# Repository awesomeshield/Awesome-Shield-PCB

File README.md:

# Awesome Shield PCB

This repo is for Awesome Shield hardware development.

## Branches

The branch `unusedVariants` is used to retain version history of variants that have been deprecated.

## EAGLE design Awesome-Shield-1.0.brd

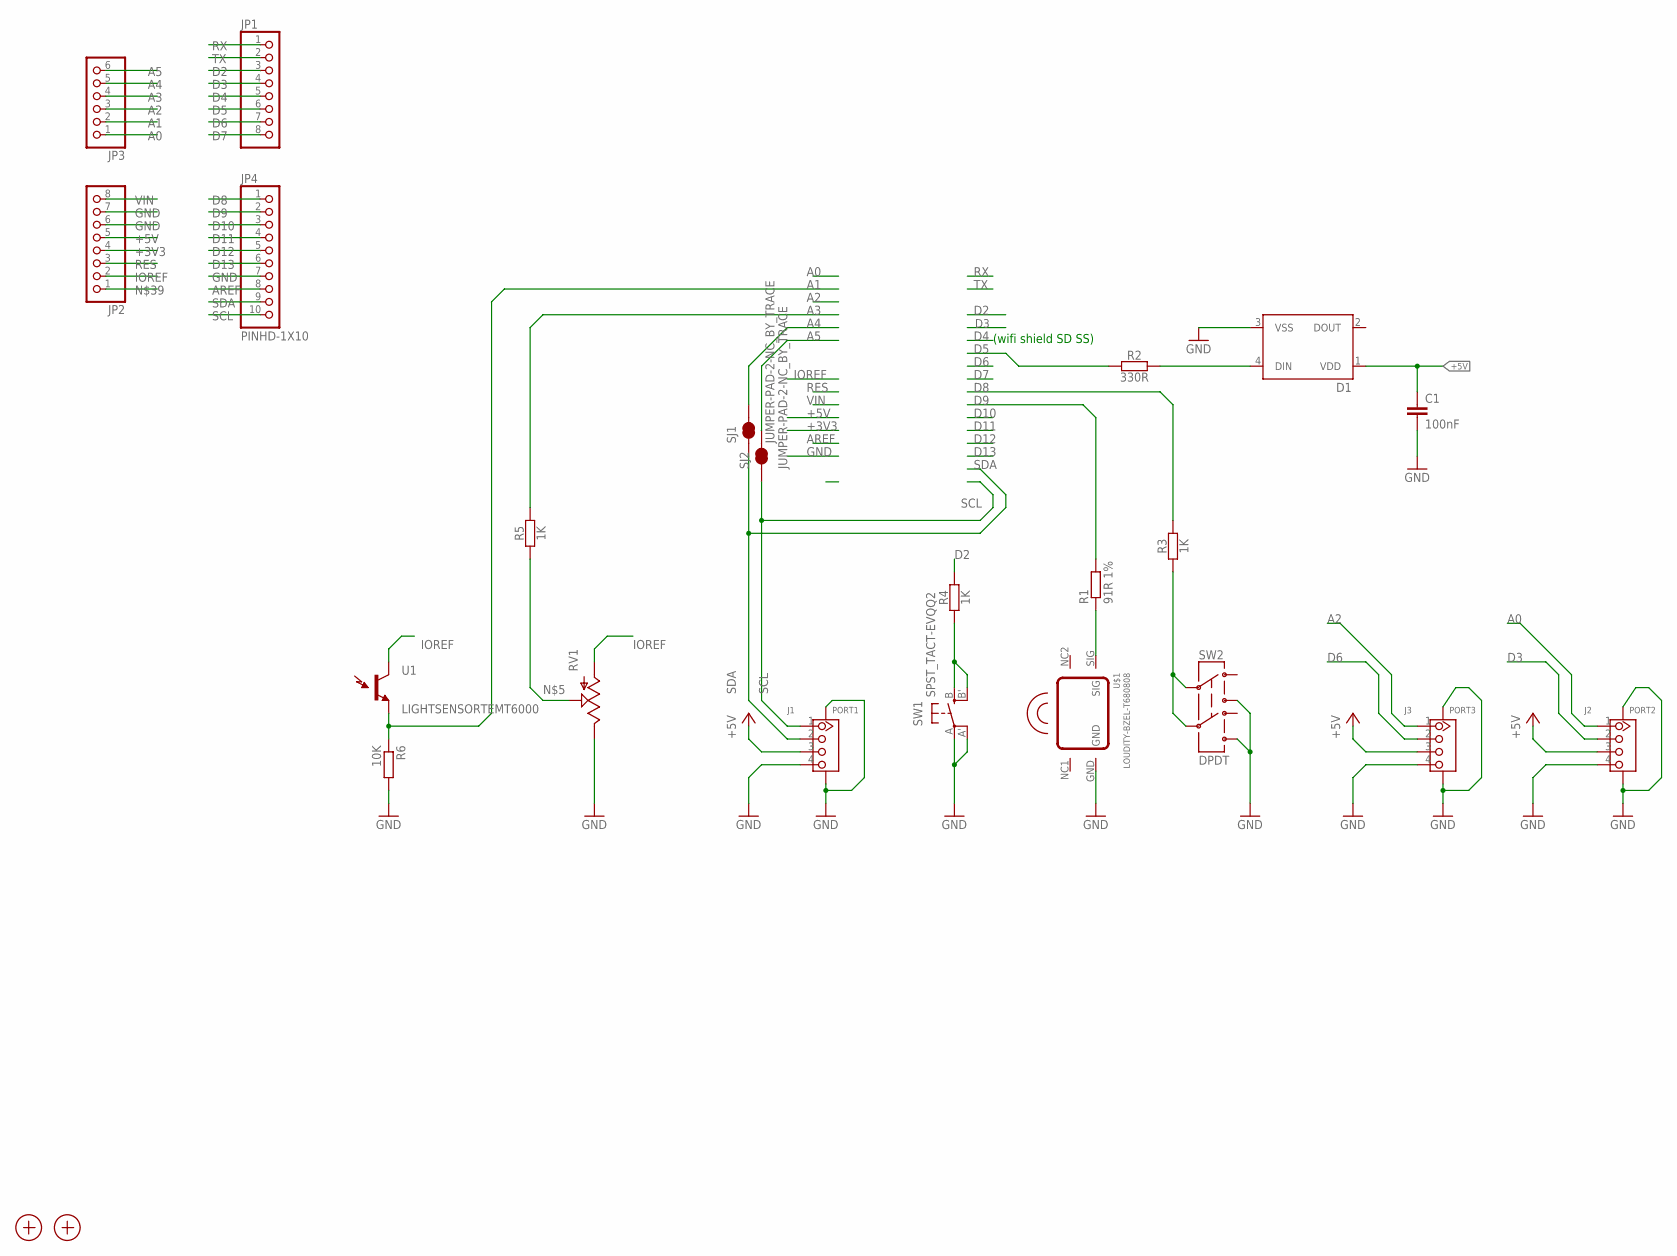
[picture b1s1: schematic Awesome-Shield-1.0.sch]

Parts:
C1: 100nF; C0603
D1: WS2812B
J1: PORT1; HW4-SMD-2.0
J2: PORT2; HW4-SMD-2.0
J3: PORT3; HW4-SMD-2.0
JP1, JP2: PINHD-1X8CLEANBIG; 1X08-CLEANBIG
JP3: PINHD-1X6CLEAN; 1X06-CLEAN
JP4: PINHD-1X10; 1X10-BIG
R1: 91R 1%; R1206
R2: 330R; C1206
R3, R4, R5: 1K; C0603
R6: 10K; R1206
RV1: POT; ALPS_POT
SJ1, SJ2: JUMPER-PAD-2-NC_BY_TRACE; PAD-JUMPER-2-NC_BY_TRACE_YES_SILK
SW1: SPST_TACT-EVQQ2; EVQ-Q2
SW2: DPDT; AYZ0202
U1: LIGHTSENSORTEMT6000; TEMT6000-SEN
U$1: LOUDITY-BZEL-T680808; SMT-68
X1, X2: PASSER-07; PASSER_07MM

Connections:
+3V3: JP2.4
+5V: C1.1, D1.1 (VDD), J1.3, J2.3, J3.3, JP2.5
A0: J2.1, JP3.1
A1: JP3.2, R6.1, U1.EMITTER (E1)
A2: J3.1, JP3.3
A3: JP3.4, R5.2
A4: JP3.5, SJ1.2
A5: JP3.6, SJ2.2
AREF: JP4.8
D2: JP1.3, R4.2
D3: J2.2, JP1.4
D4: JP1.5
D5: JP1.6, R2.1
D6: J3.2, JP1.7
D7: JP1.8
D8: JP4.1, R3.2
D9: JP4.2, R1.2
D10: JP4.3
D11: JP4.4
D12: JP4.5
D13: JP4.6
GND: C1.2, D1.3 (VSS), J1.4, J1.SS1, J1.SS2, J2.4, J2.SS1, J2.SS2, J3.4, J3.SS1, J3.SS2, JP2.6, JP2.7, JP4.7, R6.2, RV1.P$1 (E), SW1.A, SW1.A' (P1), SW2.3, SW2.6, U$1.GND
IOREF: JP2.2, RV1.P$3 (A), U1.COLLECTOR (C1)
unnamed: R1.1, U$1.SIG
unnamed: D1.4 (DIN), R2.2
unnamed: R3.1, SW2.2, SW2.5
unnamed: R5.1, RV1.P$2 (S)
unnamed: R4.1, SW1.B (S), SW1.B' (S1)
RES: JP2.3
RX: JP1.1
SCL: J1.1, JP4.10, SJ2.1
SDA: J1.2, JP4.9, SJ1.1
TX: JP1.2
VIN: JP2.8

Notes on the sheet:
(wifi shield SD SS)

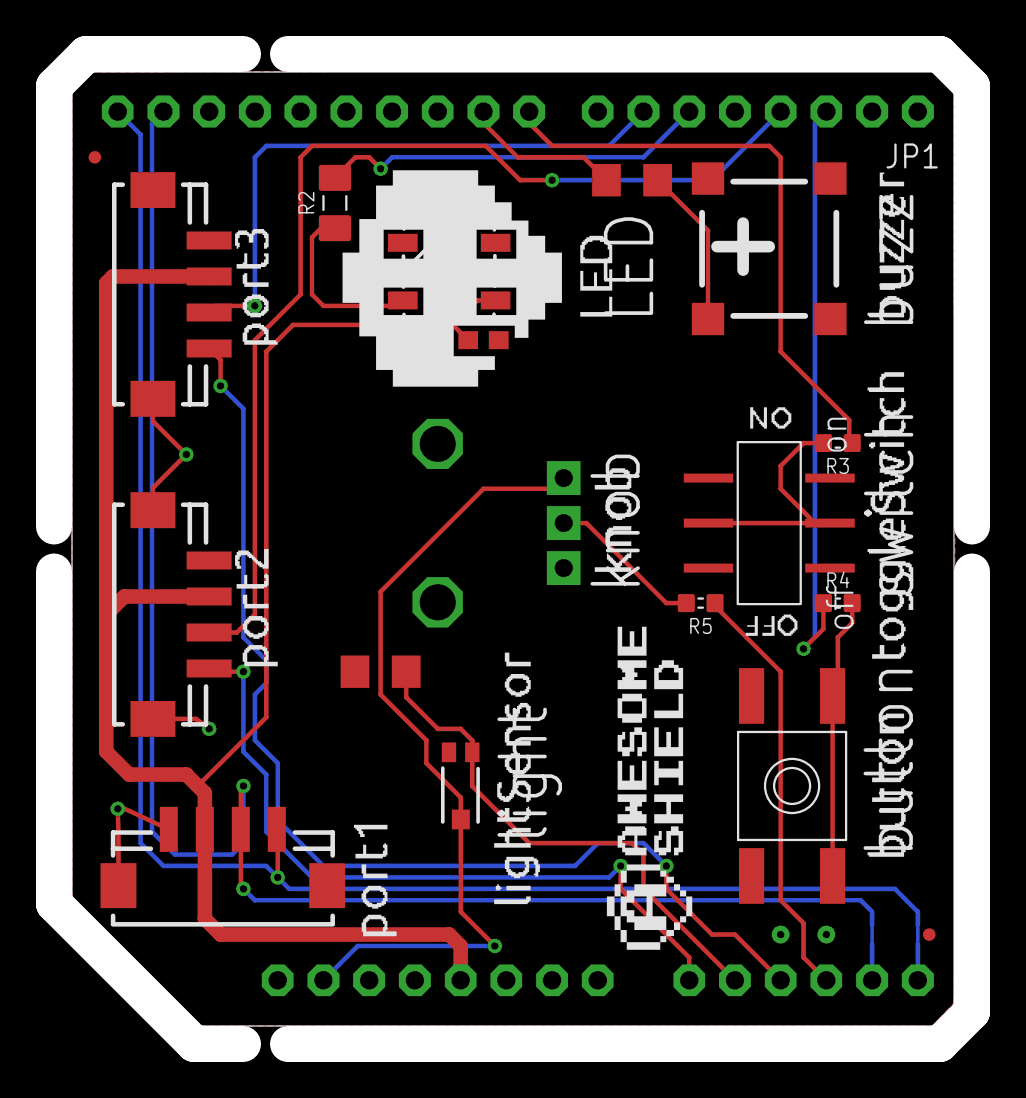
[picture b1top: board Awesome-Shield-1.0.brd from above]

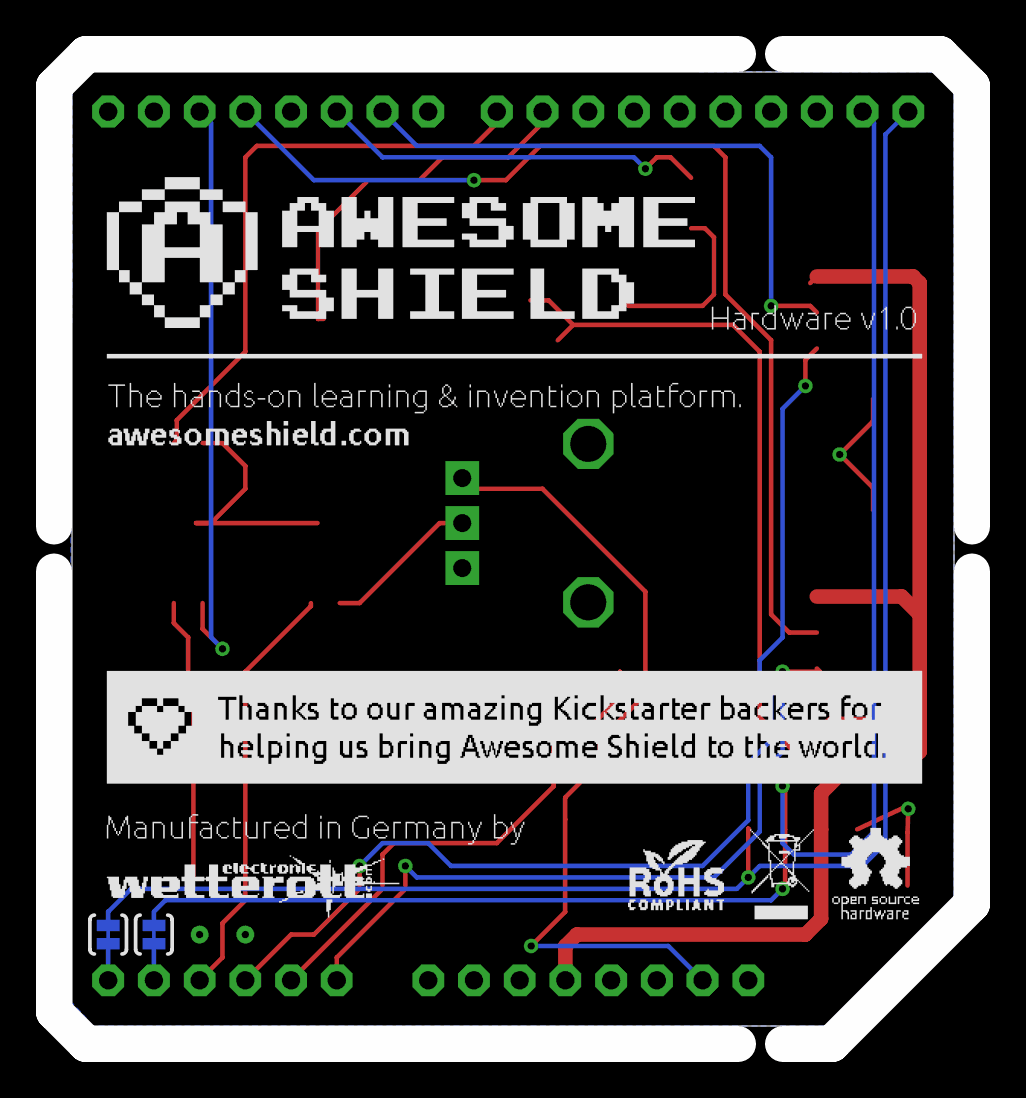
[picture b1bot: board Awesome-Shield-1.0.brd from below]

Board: 2 copper layers, 51.0 x 55.0 mm, 24 parts (2 on the bottom side), 22 nets.

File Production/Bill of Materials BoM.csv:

Manufacturer,Manufacturer Part Number (MPN),REFDES,Quantity,Mount Type,Package,Specs,Data Sheet,Notes
"Shenzhen NS-Tech Co.,Ltd.",1125S-SMT-4P,"J1, J2, J3",3,SMT,4pin connector,"4pin connector, pitch 2.00mm",http://www.seeedstudio.com/depot/images/opl/datasheet/347009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,Manufacturer page: http://www.nstech.com.cn/en/products_1.asp?menuid=19&menuid2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
4UConnector,18164,"JP1, JP2",2,THT,socket header,"1x8, 2.54mm pitch",http://www.4uconnector.com/online/object/4udrawing/18164.pdf,
4UConnector,18169,JP3,1,THT,socket header,"1x6, 2.54mm pitch",http://www.4uconnector.com/online/object/4udrawing/18169.pdf,
4UConnector,18163,JP4,1,THT,socket header,"1x10, 2.54mm pitch",http://www.4uconnector.com/online/object/4udrawing/18163.pdf,
Shenzhen Worldsemi Co.,ws2812b,LED1,1,SMT,5050,RGB,http://www.seeedstudio.com/document/pdf/WS2812B%20Datasheet.pdf,
Panasonic Electronic Components,ERJ-8GEYJ103V,R6,1,SMT,1206,10K,http://industrial.panasonic.com/ww/products/resistors/chip-r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,
AVX,0603YC104KAT2A,C1,1,SMT,0603,100nF,http://www.tme.eu/en/Document/667fe6e7748c0ed1675574c6bf64b7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,
Royal Ohm,1206S4F910JT5E,R1,1,SMT,1206,91R +/- 1%,http://www.tme.eu/en/Document/13f9d0766a2524c5bd28b9996aed3c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,
ALPS,RK09K1130A8G,RV1,1,THT,"vertical mount, pot",10K,http://www.alps.com/prod/info/E/HTML/Potentiometer/RotaryPot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,
LOUDITY,LD-BZEL-T68-0808,SG1,1,SMT,8.5 x 8.5 x 3.6mm,,http://www.tme.eu/de/Document/4d922506d0f83f2ef88b8a517d03f5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,buzzer
Schurter,1301.9314,SW1,1,SMT,"square, gull wing",TACT,http://www.schurter.com/bundles/snceschurter/epim/_ProdPool_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,
TME,MSS-2235S,SW2,1,SMT,"rect, gull wing","slide, DPDT",http://www.tme.eu/en/details/mss-2235s/slide-switches/,
Vishay,TEMT6000X01,U1,1,SMT,1206,,http://www.vishay.com/docs/81579/temt6000.pdf,
,,R2,1,SMT,1206,330R,,
,,"R3, R4, R5",3,SMT,1603,1K,,
TOTAL,,,16,,,,,

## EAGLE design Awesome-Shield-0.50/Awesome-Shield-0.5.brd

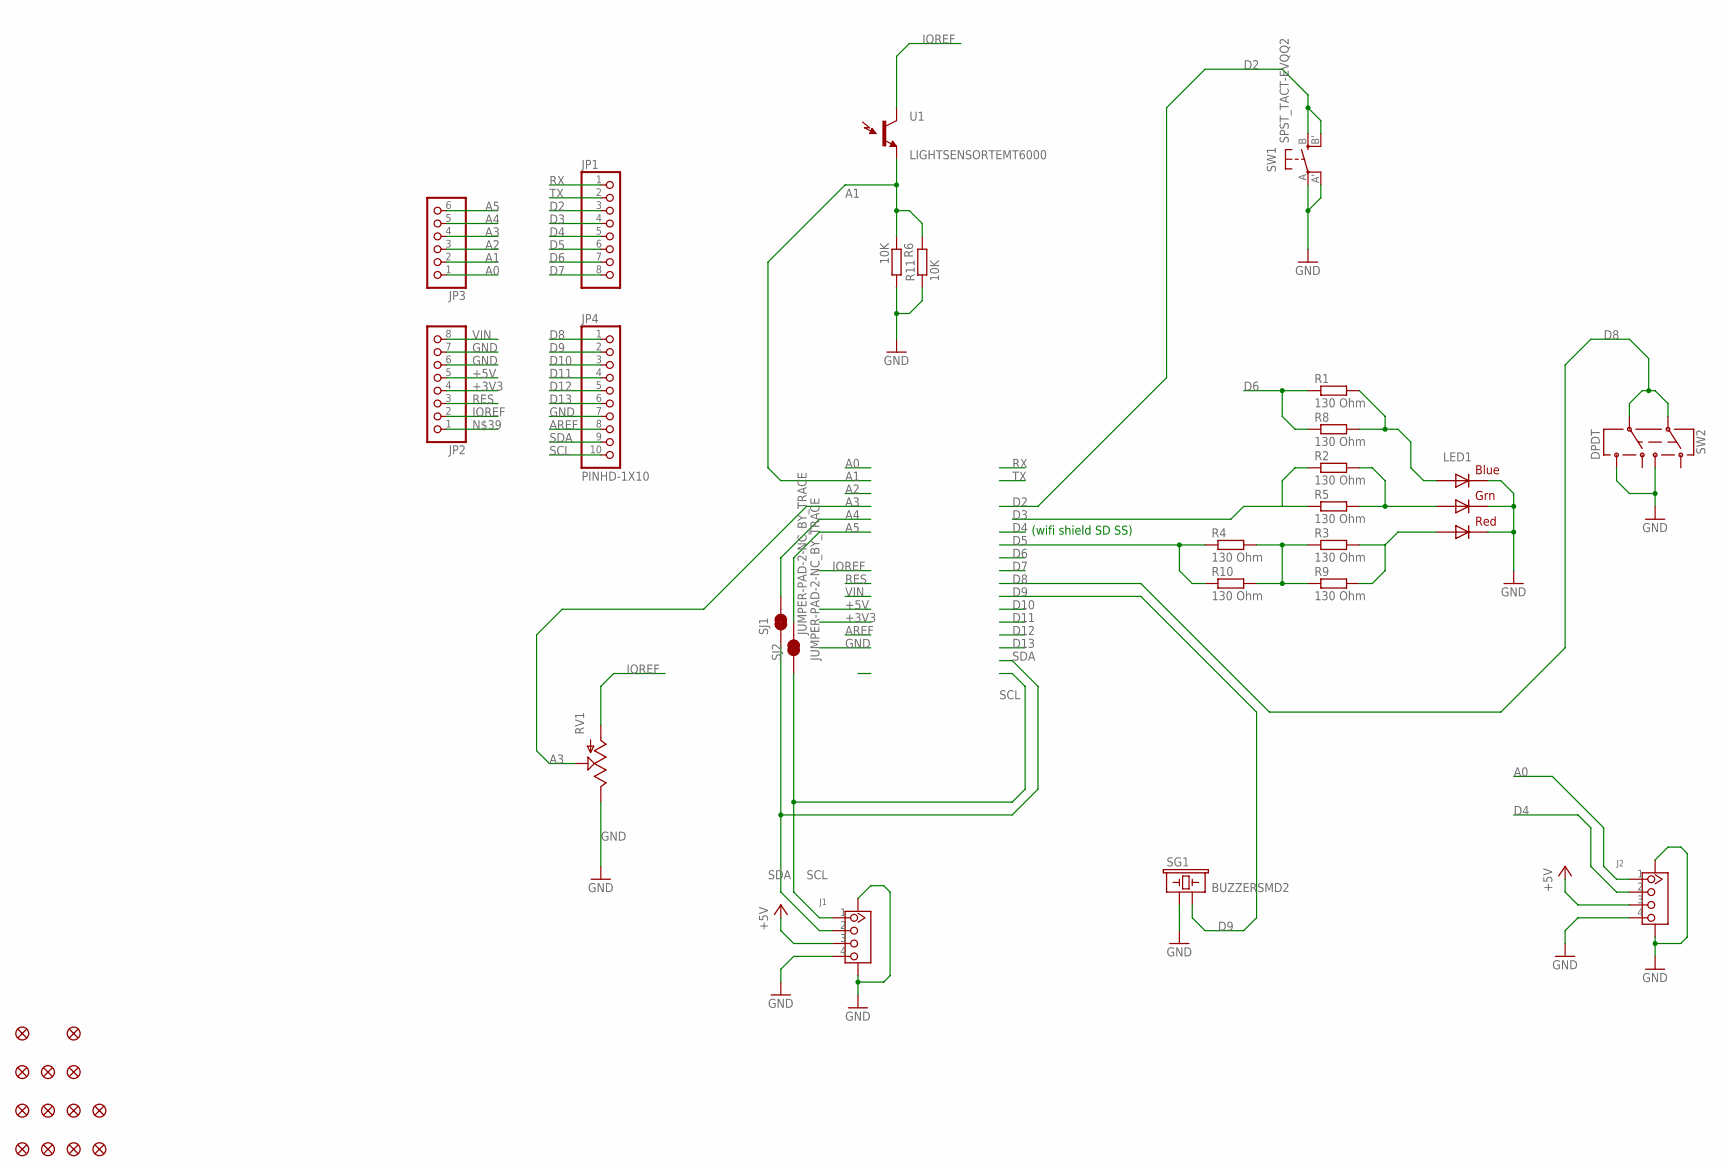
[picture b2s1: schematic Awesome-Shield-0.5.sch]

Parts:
FID1, FID2, FID3, FID4: FIDUCIAL1X2; FIDUCIAL-1X2
FID5, FID6, FID7, FID8, FID9, FID10, FID11, FID13, FID15: FIDUCIALUFIDUCIAL; MICRO-FIDUCIAL
J1, J2: GROVE-CONNECTOR-SMD(4+2P-2.0); HW4-SMD-2.0
JP1, JP2: PINHD-1X8CLEANBIG; 1X08-CLEANBIG
JP3: PINHD-1X6CLEAN; 1X06-CLEAN
JP4: PINHD-1X10; 1X10-BIG
LED1: RGBLED5050
R1, R2, R3, R4: 130 Ohm; R1206
R5, R8, R9, R10: 130 Ohm; R0603
R6: 10K; R1206
R11: 10K; R0603
RV1: POT; ALPS_POT
SG1: BUZZERSMD2; BUZZER-CCV
SJ1, SJ2: JUMPER-PAD-2-NC_BY_TRACE; PAD-JUMPER-2-NC_BY_TRACE_YES_SILK
SW1: SPST_TACT-EVQQ2; EVQ-Q2
SW2: DPDT; AYZ0202
U1: LIGHTSENSORTEMT6000; TEMT6000-SEN

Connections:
+3V3: JP2.4
+5V: J1.3, J2.3, JP2.5
A0: J2.1, JP3.1
A1: JP3.2, R6.1, R11.2, U1.EMITTER (E1)
A2: JP3.3
A3: JP3.4, RV1.P$2 (S)
A4: JP3.5, SJ1.2
A5: JP3.6, SJ2.2
AREF: JP4.8
D2: JP1.3, SW1.B (S), SW1.B' (S1)
D3: JP1.4, R2.1, R5.1
D4: J2.2, JP1.5
D5: JP1.6, R4.1, R10.1
D6: JP1.7, R1.1, R8.1
D7: JP1.8
D8: JP4.1, SW2.2, SW2.5
D9: JP4.2, SG1.- (2)
D10: JP4.3
D11: JP4.4
D12: JP4.5
D13: JP4.6
GND: J1.4, J1.SS1, J1.SS2, J2.4, J2.SS1, J2.SS2, JP2.6, JP2.7, JP4.7, LED1.4 (BLUE_C), LED1.5 (RED_C), LED1.6 (GREEN_C), R6.2, R11.1, RV1.P$1 (E), SG1.+ (1), SW1.A, SW1.A' (P1), SW2.3, SW2.6
IOREF: JP2.2, RV1.P$3 (A), U1.COLLECTOR (C1)
unnamed: R3.1, R4.2, R9.1, R10.2
unnamed: LED1.2 (RED_A), R3.2, R9.2
unnamed: LED1.3 (BLUE_A), R1.2, R8.2
unnamed: LED1.1 (GREEN_A), R2.2, R5.2
RES: JP2.3
RX: JP1.1
SCL: J1.1, JP4.10, SJ2.1
SDA: J1.2, JP4.9, SJ1.1
TX: JP1.2
VIN: JP2.8

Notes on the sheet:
(wifi shield SD SS)

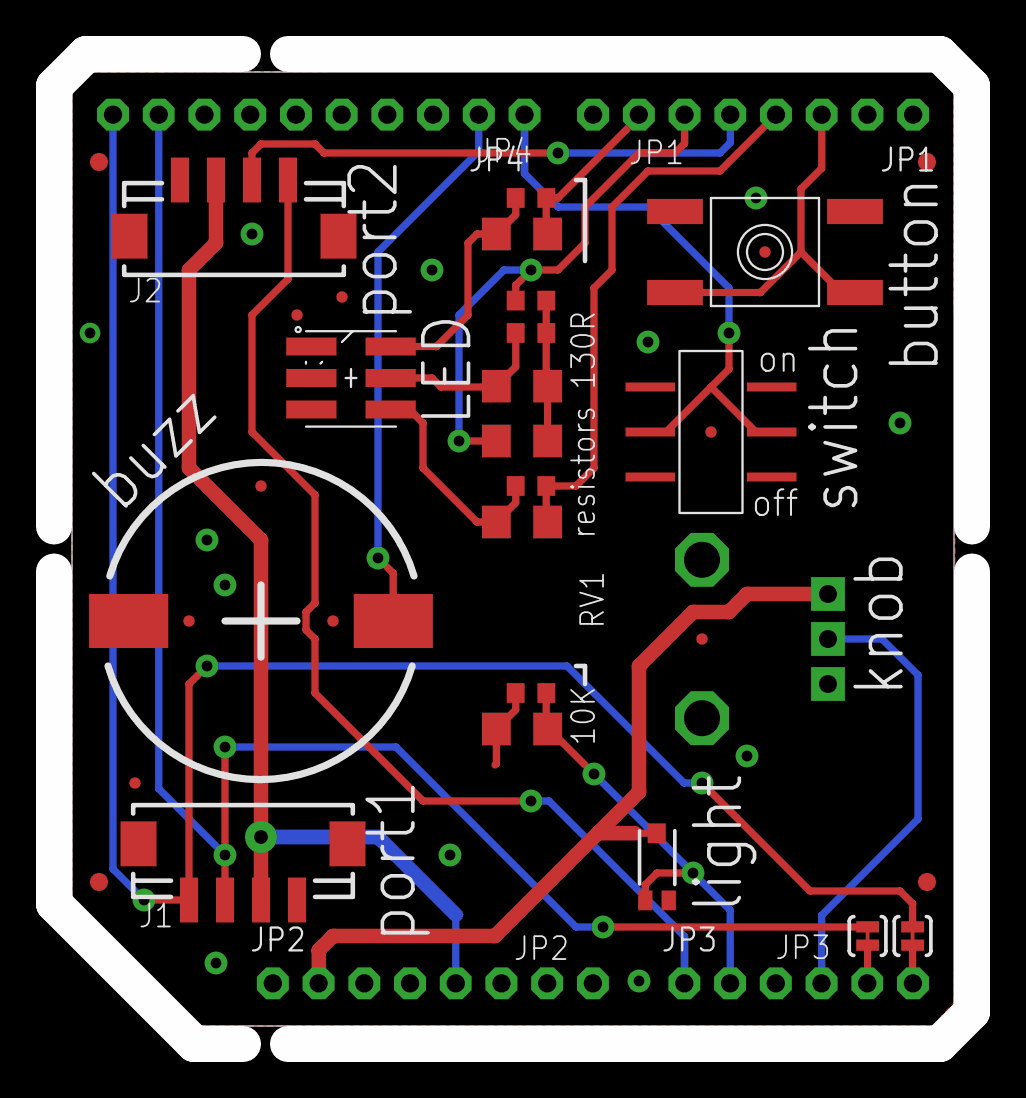
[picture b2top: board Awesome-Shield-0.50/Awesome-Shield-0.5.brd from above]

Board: 2 copper layers, 51.0 x 55.0 mm, 37 parts (0 on the bottom side), 21 nets.

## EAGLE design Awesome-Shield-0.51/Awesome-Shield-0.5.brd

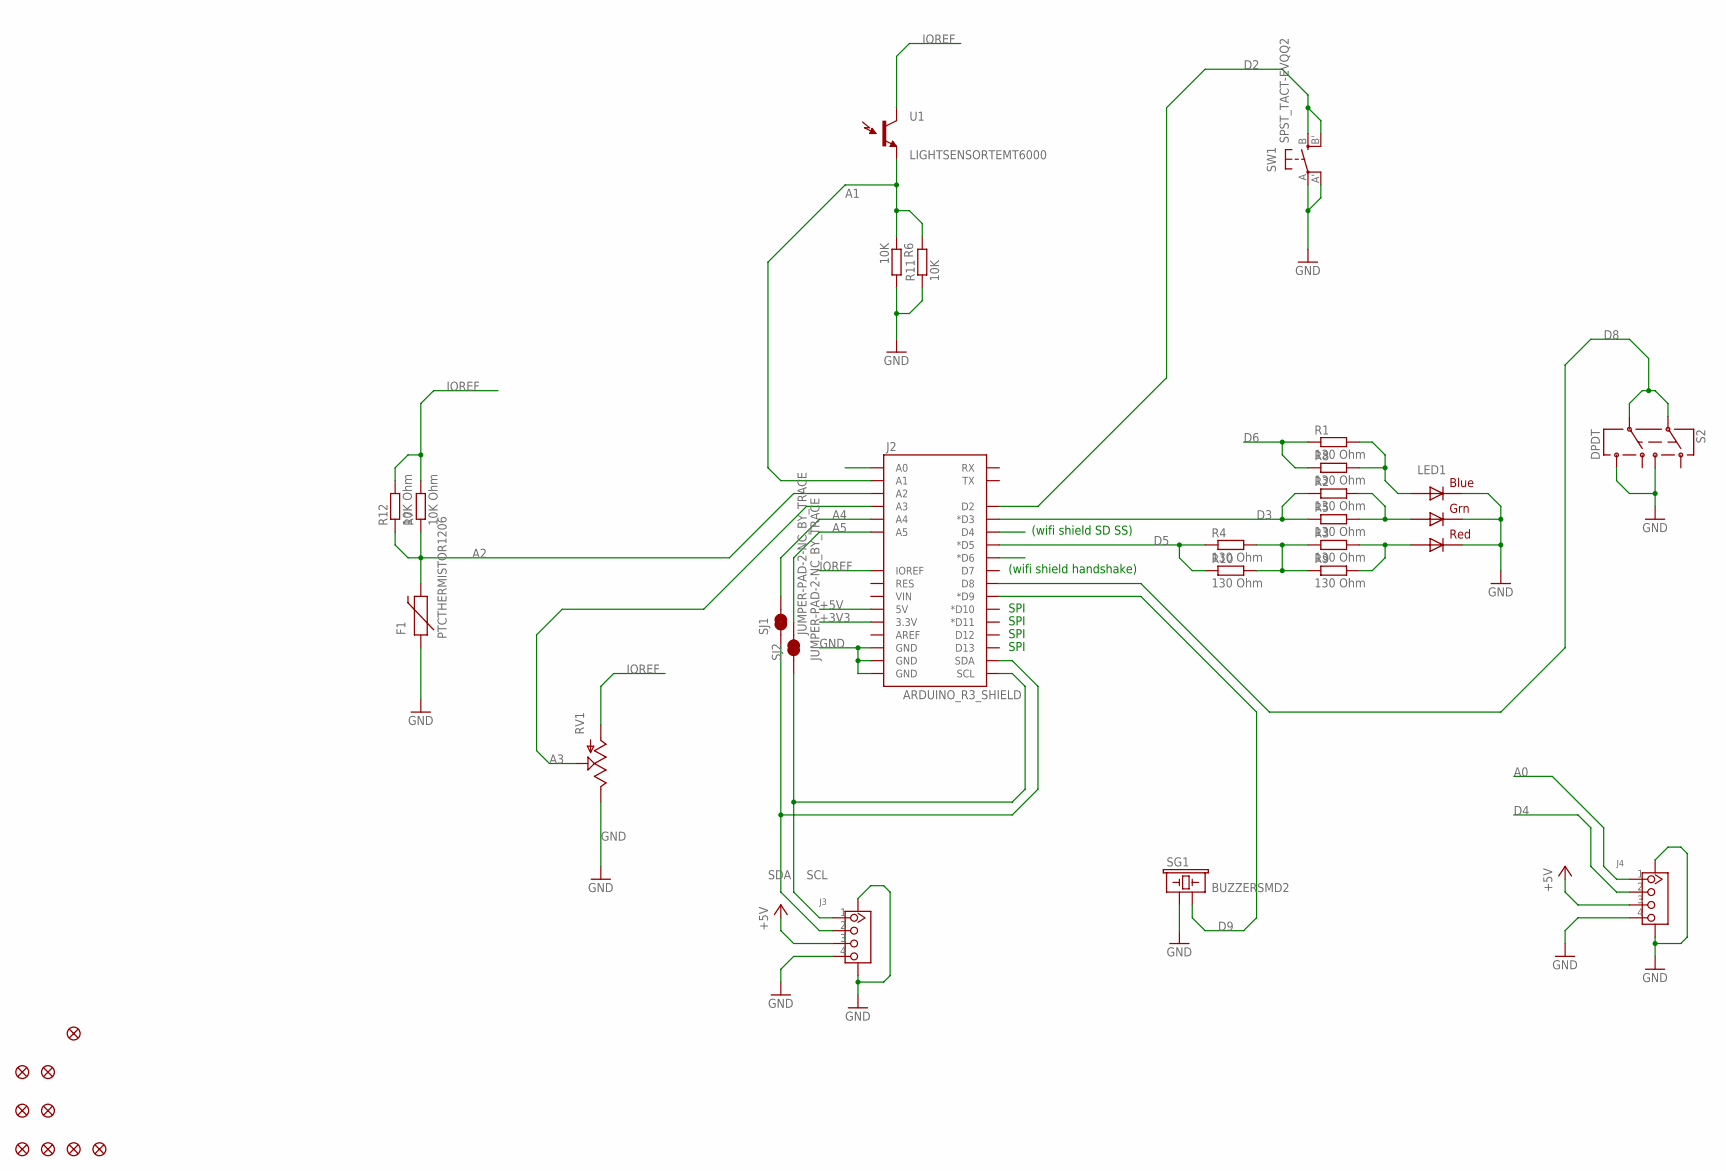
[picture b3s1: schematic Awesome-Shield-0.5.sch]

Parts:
F1: PTCTHERMISTOR1206; PTC-1206
FID1, FID2, FID3, FID4: FIDUCIAL1X2; FIDUCIAL-1X2
FID5, FID6, FID9, FID10, FID15: FIDUCIALUFIDUCIAL; MICRO-FIDUCIAL
J2: ARDUINO_R3_SHIELD; UNO_R3_SHIELD
J3, J4: GROVE-CONNECTOR-SMD(4+2P-2.0); HW4-SMD-2.0
LED1: RGBLED5050
R1, R2, R3, R4: 130 Ohm; R1206
R5, R8, R9, R10: 130 Ohm; R0603
R6: 10K; R1206
R7: 10K Ohm; R1206
R11: 10K; R0603
R12: 10K Ohm; R0603
RV1: POT; ALPS_POT
S2: DPDT; AYZ0202
SG1: BUZZERSMD2; BUZZER-CCV
SJ1, SJ2: JUMPER-PAD-2-NC_BY_TRACE; PAD-JUMPER-2-NC_BY_TRACE_YES_SILK
SW1: SPST_TACT-EVQQ2; EVQ-Q2
U1: LIGHTSENSORTEMT6000; TEMT6000-SEN

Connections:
+3V3: J2.3.3V
+5V: J2.5V, J3.3, J4.3
A0: J2.A0, J4.1
A1: J2.A1, R6.1, R11.2, U1.EMITTER (E1)
A2: F1.2, J2.A2, R7.1, R12.1
A3: J2.A3, RV1.P$2 (S)
A4: J2.A4, SJ1.2
A5: J2.A5, SJ2.2
D2: J2.D2, SW1.B (S), SW1.B' (S1)
D3: J2.D3 (*D3), R2.1, R5.1
D4: J2.D4, J4.2
D5: J2.D5 (*D5), R4.1, R10.1
D6: J2.D6 (*D6), R1.1, R8.1
D8: J2.D8, S2.2, S2.5
D9: J2.D9 (*D9), SG1.- (2)
GND: F1.1, J2.GND@0 (GND), J2.GND@1 (GND), J2.GND@2 (GND), J3.4, J3.SS1, J3.SS2, J4.4, J4.SS1, J4.SS2, LED1.4 (BLUE_C), LED1.5 (RED_C), LED1.6 (GREEN_C), R6.2, R11.1, RV1.P$1 (E), S2.3, S2.6, SG1.+ (1), SW1.A, SW1.A' (P1)
IOREF: J2.IOREF, R7.2, R12.2, RV1.P$3 (A), U1.COLLECTOR (C1)
unnamed: R3.1, R4.2, R9.1, R10.2
unnamed: LED1.2 (RED_A), R3.2, R9.2
unnamed: LED1.3 (BLUE_A), R1.2, R8.2
unnamed: LED1.1 (GREEN_A), R2.2, R5.2
SCL: J2.SCL, J3.1, SJ2.1
SDA: J2.SDA, J3.2, SJ1.1

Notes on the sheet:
SPI
(wifi shield SD SS)
(wifi shield handshake)

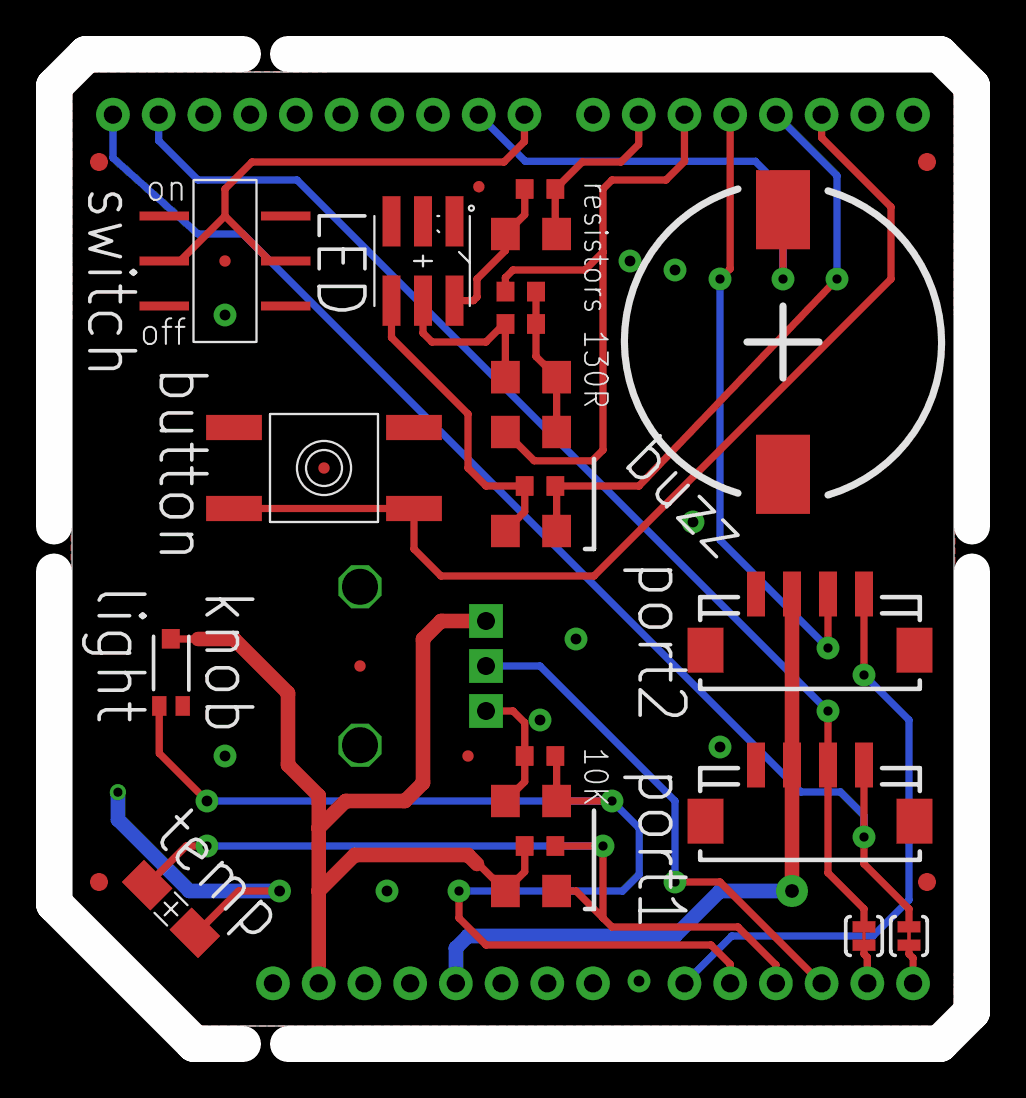
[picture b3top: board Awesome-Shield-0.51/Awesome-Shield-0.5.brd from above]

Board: 2 copper layers, 51.0 x 55.0 mm, 33 parts (0 on the bottom side), 22 nets.

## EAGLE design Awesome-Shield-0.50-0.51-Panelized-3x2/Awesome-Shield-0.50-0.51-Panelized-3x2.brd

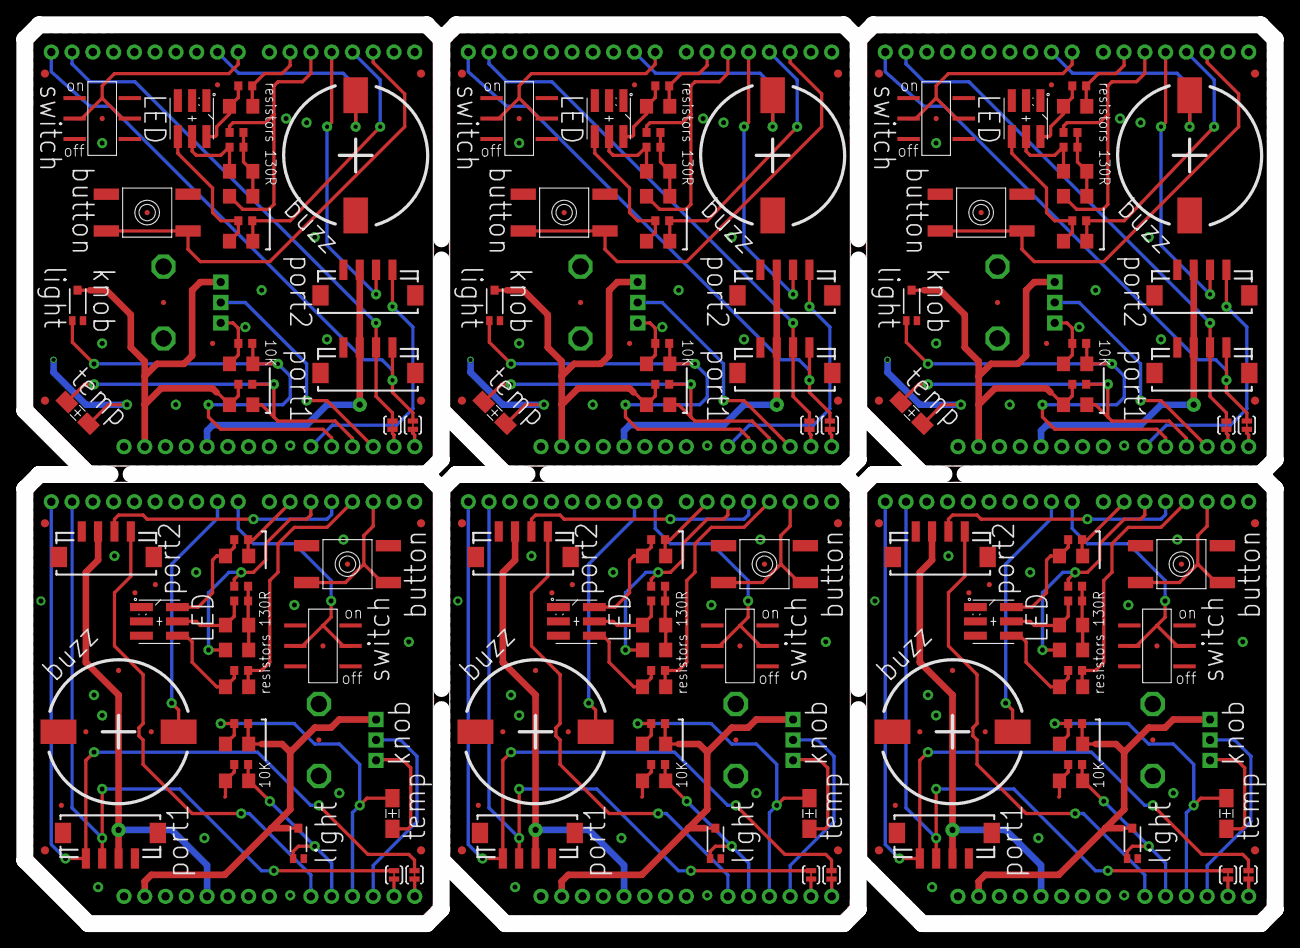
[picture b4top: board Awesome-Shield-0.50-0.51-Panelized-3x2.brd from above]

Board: 2 copper layers, 153.0 x 110.0 mm, 210 parts (0 on the bottom side), 132 nets.

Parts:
F1, F2, F3, F4, F5, F6: PTCTHERMISTOR1206; PTC-1206
FID1, FID2, FID3, FID4, FID12, FID14, FID16, FID17, FID27, FID28, FID29, FID30, FID40, FID41, FID42, FID43, FID49, FID50, FID51, FID52, FID58, FID59, FID60, FID61: FIDUCIAL1X2; FIDUCIAL-1X2
FID5, FID6, FID7, FID8, FID9, FID10, FID11, FID13, FID15, FID18, FID19, FID20, FID21, FID22, FID23, FID24, FID25, FID26, FID31, FID32, FID33, FID34, FID35, FID36, FID37, FID38, FID39, FID44, FID45, FID46, FID47, FID48, FID53, FID54, FID55, FID56, FID57, FID62, FID63, FID64, FID65, FID66: FIDUCIALUFIDUCIAL; MICRO-FIDUCIAL
J1, J3, J4, J5, J7, J8, J10, J11, J13, J14, J16, J17: HW4-SMD-2.0
J2, J6, J9, J12, J15, J18: ARDUINO_R3_SHIELD; UNO_R3_SHIELD
LED1, LED2, LED3, LED4, LED5, LED6: RGBLED5050
R1, R2, R3, R4, R13, R14, R15, R18, R25, R26, R27, R30, R37, R38, R39, R42, R49, R50, R51, R54, R61, R62, R63, R66: 130 Ohm; R1206
R5, R8, R9, R10, R19, R20, R21, R22, R31, R32, R33, R34, R43, R44, R45, R46, R55, R56, R57, R58, R67, R68, R69, R70: 130 Ohm; R0603
R6, R16, R28, R40, R52, R64: 10K; R1206
R7, R17, R29, R41, R53, R65: 10K Ohm; R1206
R11, R23, R35, R47, R59, R71: 10K; R0603
R12, R24, R36, R48, R60, R72: 10K Ohm; R0603
RV1, RV2, RV3, RV4, RV5, RV6: ALPS_POT
S1, S2, S3, S4, S5, S6: DPDT; AYZ0202
SG1, SG2, SG3, SG4, SG5, SG6: BUZZERSMD2; BUZZER-CCV
SJ1, SJ2, SJ3, SJ4, SJ5, SJ6, SJ7, SJ8, SJ9, SJ10, SJ11, SJ12: JUMPER-PAD-2-NC_BY_TRACE; PAD-JUMPER-2-NC_BY_TRACE_YES_SILK
SW1, SW2, SW3, SW4, SW5, SW6: SPST_TACT-EVQQ2; EVQ-Q2
U1, U2, U3, U4, U5, U6: LIGHTSENSORTEMT6000; TEMT6000-SEN

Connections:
+5V: J2.5V, J3.3, J4.3
+5V1: J1.3, J5.3, J6.5V
+5V2: J7.3, J8.3, J9.5V
+5V3: J10.3, J11.3, J12.5V
+5V4: J13.3, J14.3, J15.5V
+5V5: J16.3, J17.3, J18.5V
A0: J2.A0, J4.1
A1: J2.A1, R6.1, R11.2, U1.EMITTER
A2: F1.2, J2.A2, R7.1, R12.1
A3: J2.A3, RV1.P$2
A4: J2.A4, SJ1.2
A5: J2.A5, SJ2.2
A6: J6.A1, R16.1, R23.2, U2.EMITTER
A7: F2.2, J6.A2, R17.1, R24.1
A8: J5.1, J6.A0
A9: J6.A5, SJ4.2
A10: J6.A4, SJ3.2
A11: J6.A3, RV2.P$2
A12: J9.A1, R28.1, R35.2, U3.EMITTER
A13: F3.2, J9.A2, R29.1, R36.1
A14: J8.1, J9.A0
A15: J9.A5, SJ6.2
A16: J9.A4, SJ5.2
A17: J9.A3, RV3.P$2
A18: J12.A1, R40.1, R47.2, U4.EMITTER
A19: F4.2, J12.A2, R41.1, R48.1
A20: J11.1, J12.A0
A21: J12.A5, SJ8.2
A22: J12.A4, SJ7.2
A23: J12.A3, RV4.P$2
A24: J15.A1, R52.1, R59.2, U5.EMITTER
A25: F5.2, J15.A2, R53.1, R60.1
A26: J14.1, J15.A0
A27: J15.A5, SJ10.2
A28: J15.A4, SJ9.2
A29: J15.A3, RV5.P$2
A30: J18.A1, R64.1, R71.2, U6.EMITTER
A31: F6.2, J18.A2, R65.1, R72.1
A32: J17.1, J18.A0
A33: J18.A5, SJ12.2
A34: J18.A4, SJ11.2
A35: J18.A3, RV6.P$2
D1: J6.D2, SW2.B, SW2.B'
D2: J2.D2, SW1.B, SW1.B'
D3: J2.D3, R2.1, R5.1
D4: J2.D4, J4.2
D5: J2.D5, R4.1, R10.1
D6: J2.D6, R1.1, R8.1
D7: J6.D6, R13.1, R19.1
D8: J2.D8, S2.2, S2.5
D9: J2.D9, SG1.-
D10: J6.D8, S1.2, S1.5
D11: J6.D9, SG2.-
D12: J5.2, J6.D4
D13: J6.D5, R18.1, R22.1
D14: J6.D3, R14.1, R20.1
D15: J9.D2, SW3.B, SW3.B'
D16: J9.D6, R25.1, R31.1
D17: J9.D8, S3.2, S3.5
D18: J9.D9, SG3.-
D19: J8.2, J9.D4
D20: J9.D5, R30.1, R34.1
D21: J9.D3, R26.1, R32.1
D22: J12.D2, SW4.B, SW4.B'
D23: J12.D6, R37.1, R43.1
D24: J12.D8, S4.2, S4.5
D25: J12.D9, SG4.-
D26: J11.2, J12.D4
D27: J12.D5, R42.1, R46.1
D28: J12.D3, R38.1, R44.1
D29: J15.D2, SW5.B, SW5.B'
D30: J15.D6, R49.1, R55.1
D31: J15.D8, S5.2, S5.5
D32: J15.D9, SG5.-
D33: J14.2, J15.D4
D34: J15.D5, R54.1, R58.1
D35: J15.D3, R50.1, R56.1
D36: J18.D2, SW6.B, SW6.B'
D37: J18.D6, R61.1, R67.1
D38: J18.D8, S6.2, S6.5
D39: J18.D9, SG6.-
D40: J17.2, J18.D4
D41: J18.D5, R66.1, R70.1
D42: J18.D3, R62.1, R68.1
GND: F1.1, J2.GND@0, J2.GND@1, J2.GND@2, J3.4, J3.SS1, J3.SS2, J4.4, J4.SS1, J4.SS2, LED1.4, LED1.5, LED1.6, R6.2, R11.1, RV1.P$1, S2.3, S2.6, SG1.+, SW1.A, SW1.A'
GND1: F2.1, J1.4, J1.SS1, J1.SS2, J5.4, J5.SS1, J5.SS2, J6.GND@0, J6.GND@1, J6.GND@2, LED2.4, LED2.5, LED2.6, R16.2, R23.1, RV2.P$1, S1.3, S1.6, SG2.+, SW2.A, SW2.A'
GND2: F3.1, J7.4, J7.SS1, J7.SS2, J8.4, J8.SS1, J8.SS2, J9.GND@0, J9.GND@1, J9.GND@2, LED3.4, LED3.5, LED3.6, R28.2, R35.1, RV3.P$1, S3.3, S3.6, SG3.+, SW3.A, SW3.A'
GND3: F4.1, J10.4, J10.SS1, J10.SS2, J11.4, J11.SS1, J11.SS2, J12.GND@0, J12.GND@1, J12.GND@2, LED4.4, LED4.5, LED4.6, R40.2, R47.1, RV4.P$1, S4.3, S4.6, SG4.+, SW4.A, SW4.A'
GND4: F5.1, J13.4, J13.SS1, J13.SS2, J14.4, J14.SS1, J14.SS2, J15.GND@0, J15.GND@1, J15.GND@2, LED5.4, LED5.5, LED5.6, R52.2, R59.1, RV5.P$1, S5.3, S5.6, SG5.+, SW5.A, SW5.A'
GND5: F6.1, J16.4, J16.SS1, J16.SS2, J17.4, J17.SS1, J17.SS2, J18.GND@0, J18.GND@1, J18.GND@2, LED6.4, LED6.5, LED6.6, R64.2, R71.1, RV6.P$1, S6.3, S6.6, SG6.+, SW6.A, SW6.A'
IOREF: J2.IOREF, R7.2, R12.2, RV1.P$3, U1.COLLECTOR
IOREF1: J6.IOREF, R17.2, R24.2, RV2.P$3, U2.COLLECTOR
IOREF2: J9.IOREF, R29.2, R36.2, RV3.P$3, U3.COLLECTOR
IOREF3: J12.IOREF, R41.2, R48.2, RV4.P$3, U4.COLLECTOR
IOREF4: J15.IOREF, R53.2, R60.2, RV5.P$3, U5.COLLECTOR
IOREF5: J18.IOREF, R65.2, R72.2, RV6.P$3, U6.COLLECTOR
unnamed: LED2.2, R15.2, R21.2
unnamed: R3.1, R4.2, R9.1, R10.2
unnamed: LED1.2, R3.2, R9.2
unnamed: R15.1, R18.2, R21.1, R22.2
unnamed: LED2.3, R13.2, R19.2
unnamed: LED2.1, R14.2, R20.2
unnamed: LED3.2, R27.2, R33.2
unnamed: LED1.3, R1.2, R8.2
unnamed: LED1.1, R2.2, R5.2
unnamed: R27.1, R30.2, R33.1, R34.2
unnamed: LED3.3, R25.2, R31.2
unnamed: LED3.1, R26.2, R32.2
unnamed: LED4.2, R39.2, R45.2
unnamed: R39.1, R42.2, R45.1, R46.2
unnamed: LED4.3, R37.2, R43.2
unnamed: LED4.1, R38.2, R44.2
unnamed: LED5.2, R51.2, R57.2
unnamed: R51.1, R54.2, R57.1, R58.2
unnamed: LED5.3, R49.2, R55.2
unnamed: LED5.1, R50.2, R56.2
unnamed: LED6.2, R63.2, R69.2
unnamed: R63.1, R66.2, R69.1, R70.2
unnamed: LED6.3, R61.2, R67.2
unnamed: LED6.1, R62.2, R68.2
SCL: J2.SCL, J3.1, SJ2.1
SCL1: J1.1, J6.SCL, SJ4.1
SCL2: J7.1, J9.SCL, SJ6.1
SCL3: J10.1, J12.SCL, SJ8.1
SCL4: J13.1, J15.SCL, SJ10.1
SCL5: J16.1, J18.SCL, SJ12.1
SDA: J2.SDA, J3.2, SJ1.1
SDA1: J1.2, J6.SDA, SJ3.1
SDA2: J7.2, J9.SDA, SJ5.1
SDA3: J10.2, J12.SDA, SJ7.1
SDA4: J13.2, J15.SDA, SJ9.1
SDA5: J16.2, J18.SDA, SJ11.1

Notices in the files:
Awesome-Shield-0.50-0.51-Panelized-3x2/Awesome-Shield-0.50-0.51-Panelized-3x2.brd:
Hardware Designs Released under the MIT License
parts and their libraries:
SparkFun-Boards: Licensing: Creative Commons ShareAlike 4.0 International - https://creativecommons.org/licenses/by-sa/4.0
